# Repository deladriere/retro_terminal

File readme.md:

#Usage

#Software
expliquer la modif de la libraries

#todo
 Ajouter un buzzer ? plus petit

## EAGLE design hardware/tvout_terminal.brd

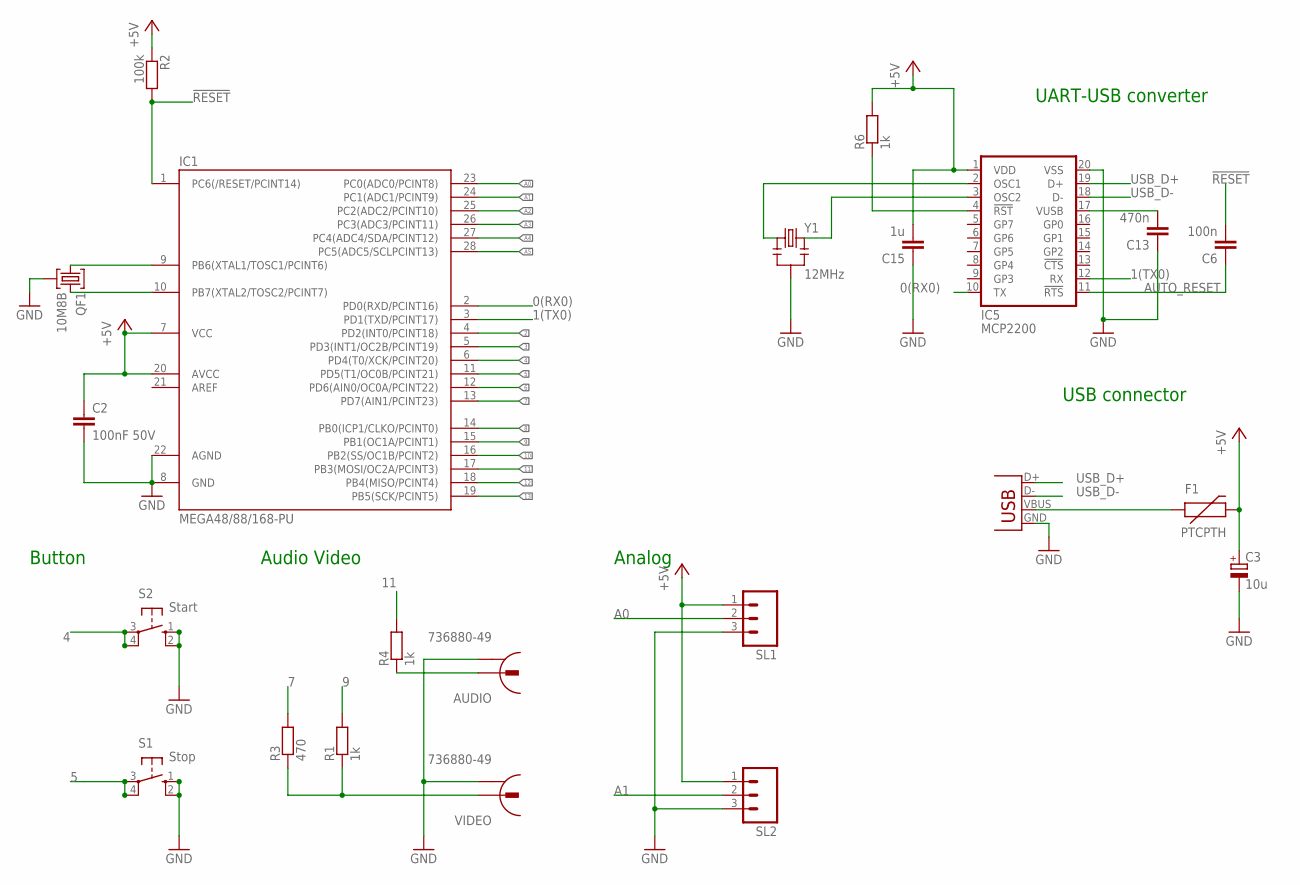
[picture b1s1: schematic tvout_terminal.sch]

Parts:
AUDIO: 736880-49
C2: 100nF 50V; C025-025X050
C3: 10u; E2,5-7
C6: 100n; CAP-PTH-SMALL
C13: 470n; CAP-PTH-SMALL
C15: 1u; CAP-PTH-SMALL
F1: PTCPTH; PTC
IC1: MEGA48/88/168-PU; DIL28-3
IC5: MCP2200; SO20
QF1: 10M8B; HC49U
R1, R4, R6: 1k; RES-AXIAL-0.4
R2: 100k; RES-AXIAL-0.4
R3: 470; RES-AXIAL-0.4
S1: Stop; B3F-10XX
S2: Start; B3F-10XX
SL1, SL2: M03; 03P
VIDEO: 736880-49
X3: USB; USB-B-PTH
Y1: 12MHz; HC49U-V-RESONATOR

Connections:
0(RX0): IC1.2 (PD0(RXD/PCINT16)), IC5.10 (TX)
1(TX0): IC1.3 (PD1(TXD/PCINT17)), IC5.12 (RX)
2: IC1.4 (PD2(INT0/PCINT18))
3: IC1.5 (PD3(INT1/OC2B/PCINT19))
4: IC1.6 (PD4(T0/XCK/PCINT20)), S2.3, S2.4 (P1)
5: IC1.11 (PD5(T1/OC0B/PCINT21)), S1.3, S1.4 (P1)
6: IC1.12 (PD6(AIN0/OC0A/PCINT22))
7: IC1.13 (PD7(AIN1/PCINT23)), R3.P$2 (2)
8: IC1.14 (PB0(ICP1/CLKO/PCINT0))
9: IC1.15 (PB1(OC1A/PCINT1)), R1.P$2 (2)
10: IC1.16 (PB2(SS/OC1B/PCINT2))
11: IC1.17 (PB3(MOSI/OC2A/PCINT3)), R4.P$2 (2)
12: IC1.18 (PB4(MISO/PCINT4))
13: IC1.19 (PB5(SCK/PCINT5))
!RESET: C6.2, IC1.1 (PC6(/RESET/PCINT14)), R2.P$2 (2)
+5V: C2.1, C3.+, C15.2, F1.P$2 (2), IC1.7 (VCC), IC1.20 (AVCC), IC5.1 (VDD), R2.P$1 (1), R6.P$2 (2), SL1.1, SL2.1
A0: IC1.23 (PC0(ADC0/PCINT8)), SL1.2
A1: IC1.24 (PC1(ADC1/PCINT9)), SL2.2
A2: IC1.25 (PC2(ADC2/PCINT10))
A3: IC1.26 (PC3(ADC3/PCINT11))
A4: IC1.27 (PC4(ADC4/SDA/PCINT12))
A5: IC1.28 (PC5(ADC5/SCLPCINT13))
AUTO_RESET: C6.1, IC5.11 (!RTS)
GND: AUDIO.2, C2.2, C3.-, C13.1, C15.1, IC1.8 (GND), IC1.22 (AGND), IC5.20 (VSS), QF1.2, S1.1 (S), S1.2 (S1), S2.1 (S), S2.2 (S1), SL1.3, SL2.3, VIDEO.2, X3.GND, Y1.GND (2)
unnamed: F1.P$1 (1), X3.VBUS
unnamed: R1.P$1 (1), R3.P$1 (1), VIDEO.1
unnamed: IC1.9 (PB6(XTAL1/TOSC1/PCINT6)), QF1.1
unnamed: AUDIO.1, R4.P$1 (1)
unnamed: IC5.3 (OSC2), Y1.2 (3)
unnamed: IC1.10 (PB7(XTAL2/TOSC2/PCINT7)), QF1.3
unnamed: C13.2, IC5.17 (VUSB)
unnamed: IC5.2 (OSC1), Y1.1
unnamed: IC5.4 (!RST), R6.P$1 (1)
USB_D+: IC5.19 (D+), X3.D+
USB_D-: IC5.18 (D-), X3.D-

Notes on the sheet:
UART-USB converter
USB connector
Button
Audio Video
Analog

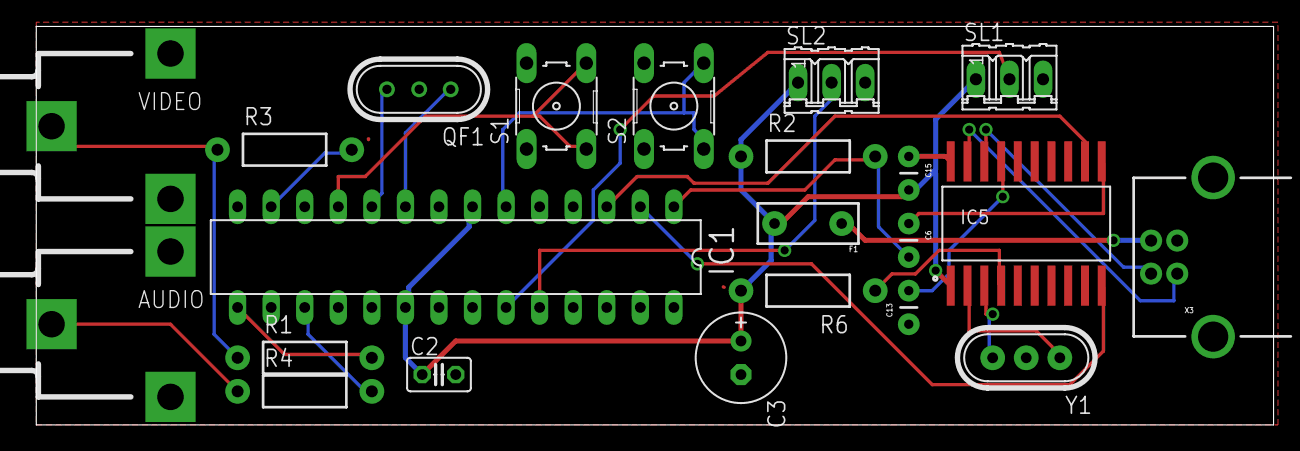
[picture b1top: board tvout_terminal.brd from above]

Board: 2 copper layers, 93.7 x 30.2 mm, 22 parts (0 on the bottom side), 24 nets.

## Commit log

2014-05-08 Updating gitignore to ignore Eagles backups
2014-05-08 removing Eagle backups
2014-05-18 remove old version of Eagle file adding code
